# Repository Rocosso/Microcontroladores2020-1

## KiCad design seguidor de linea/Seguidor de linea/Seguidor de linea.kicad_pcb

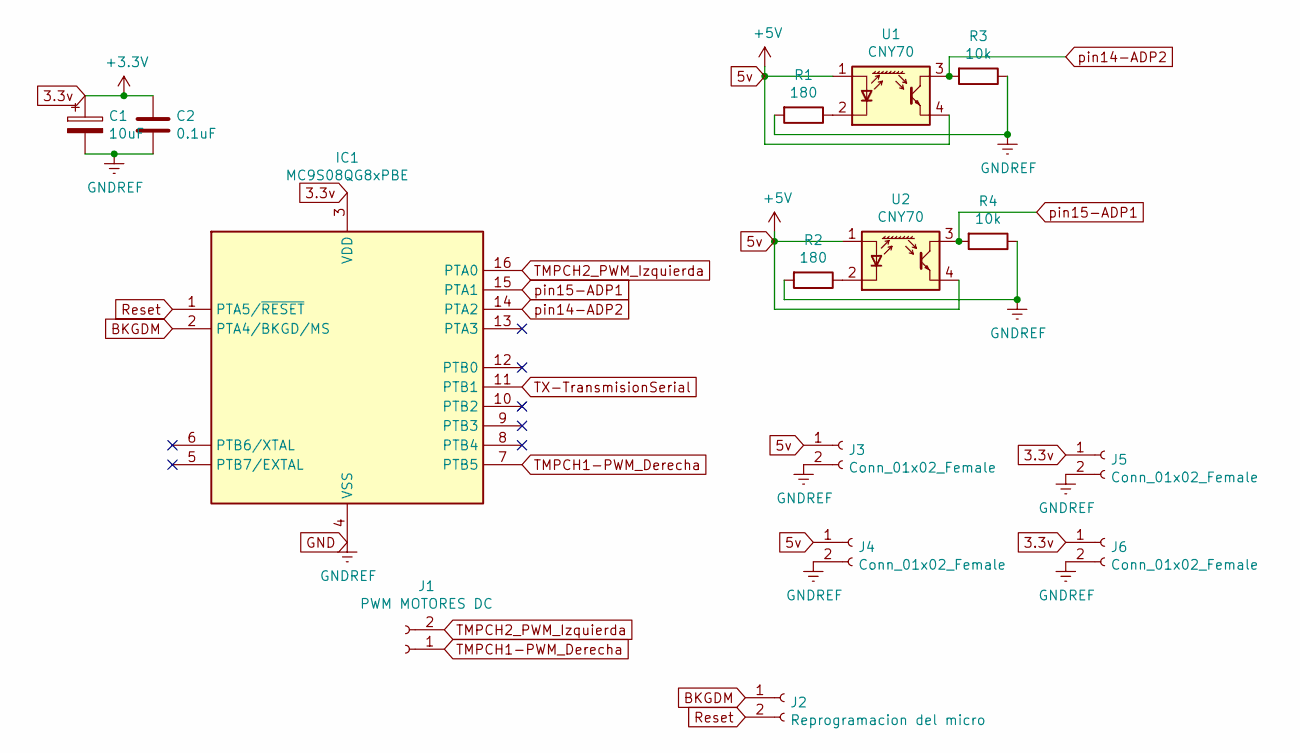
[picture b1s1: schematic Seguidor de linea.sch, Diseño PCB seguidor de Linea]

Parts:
C1: 10uF; CP_Radial_D4.0mm_P2.00mm
C2: 0.1uF; C_Disc_D4.7mm_W2.5mm_P5.00mm
IC1: MC9S08QG8xPBE; DIP-16_W7.62mm
J1: PWM MOTORES DC; PinSocket_1x02_P2.54mm_Vertical_SMD_Pin1Left
J2: Reprogramacion del micro; PinSocket_1x02_P2.54mm_Vertical_SMD_Pin1Left
J3, J4, J5, J6: Conn_01x02_Female; PinSocket_1x02_P2.54mm_Vertical_SMD_Pin1Right
R1, R2: 180; R_Axial_DIN0204_L3.6mm_D1.6mm_P1.90mm_Vertical
R3, R4: 10k; R_Axial_DIN0204_L3.6mm_D1.6mm_P1.90mm_Vertical
U1, U2: CNY70; Vishay_CNY70

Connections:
3.3v: C1.1, C2.1, IC1.3 (VDD), J5.1, J6.1
5v: J3.1, J4.1, U1.1 (A), U1.4 (E), U2.1 (A), U2.4 (E)
BKGDM: IC1.2 (PTA4/BKGD/MS), J2.1
GND: C1.2, C2.2, IC1.4 (VSS), J3.2, J4.2, J5.2, J6.2, R1.2, R2.2, R3.1, R4.1
unnamed: R1.1, U1.2 (K)
unnamed: R2.1, U2.2 (K)
Reset: IC1.1 (PTA5/~RESET), J2.2
TMPCH1-PWM_Derecha: IC1.7 (PTB5), J1.1
TMPCH2_PWM_Izquierda: IC1.16 (PTA0), J1.2
TX-TransmisionSerial: IC1.11 (PTB1)
pin14-ADP2: IC1.14 (PTA2), R3.2, U1.3 (C)
pin15-ADP1: IC1.15 (PTA1), R4.2, U2.3 (C)

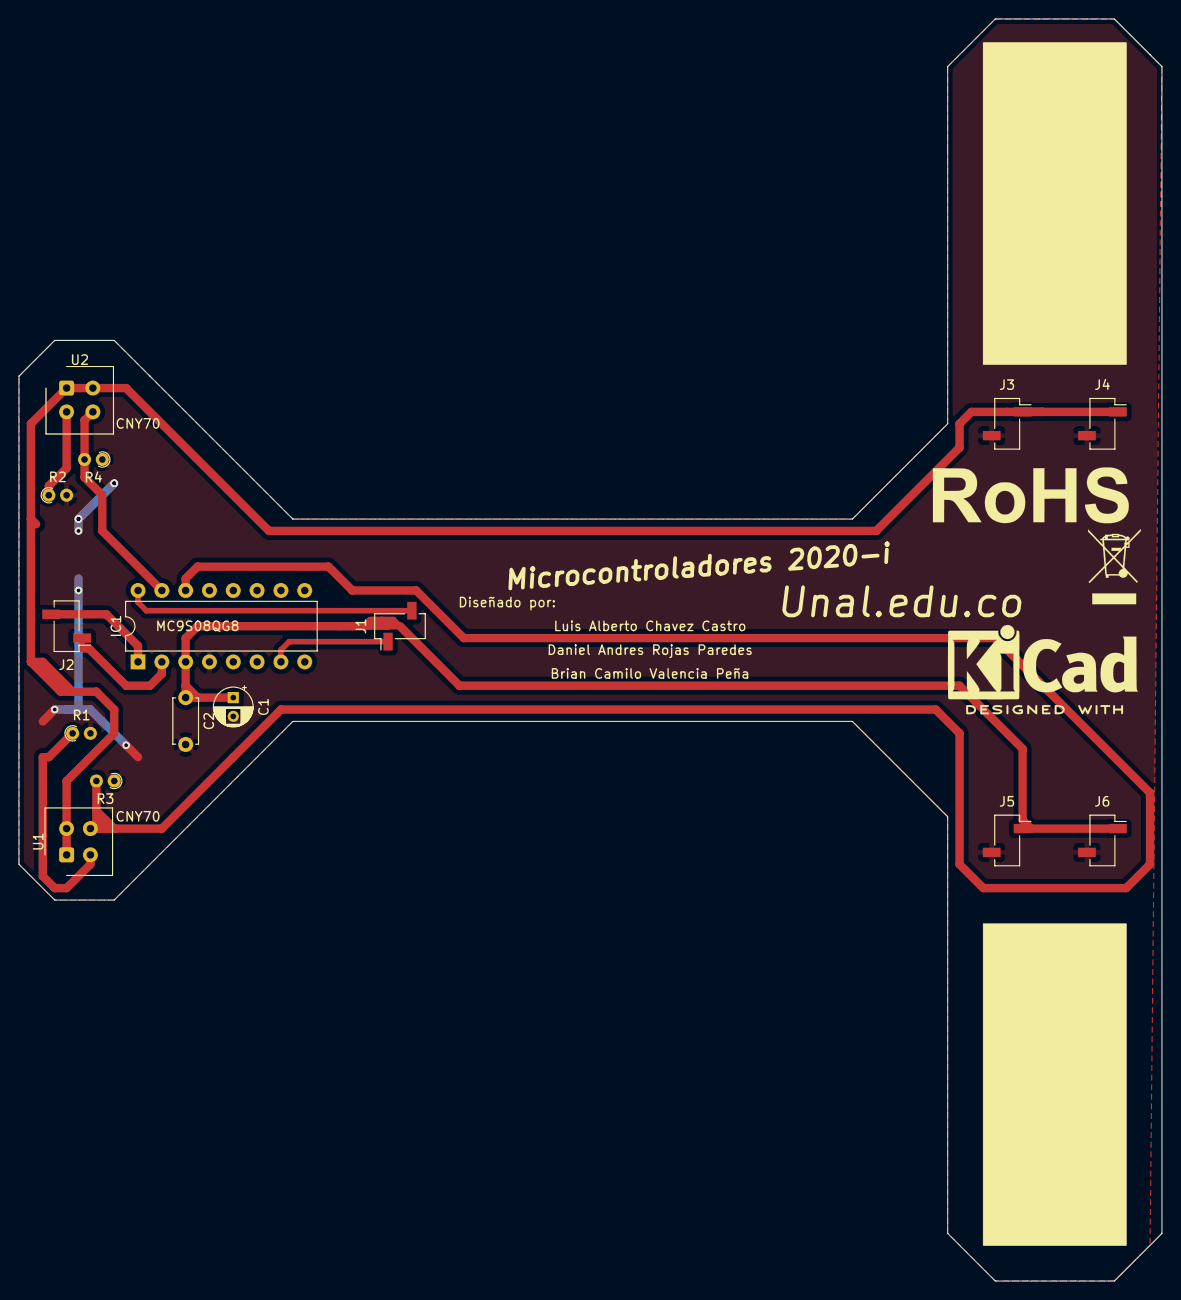
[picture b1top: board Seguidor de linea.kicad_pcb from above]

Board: 2 copper layers, 121.9 x 134.6 mm, 15 parts (0 on the bottom side), 11 nets.

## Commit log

2020-05-07 creacion del repositorio de microcontroladores
2020-05-07 creado el link al informe en overleaf
2020-05-07 actualizacion esquematico correccion tierra en LED-RGB e imagenes para el informe
2020-05-07 avance del PDF del informe del lab 1
2020-05-07 creacion carpeta lab2 y enlaces
2020-05-17 se actualizo en lab1 las fuentes de poder a 3v3, imagenes y esquematico
2020-05-17 agregados condensadores entre VCC y Vdd al esquematico
2020-05-17 se crea carpeta REFERENCE MANUAL CON DOS LIBROS, QG8 y HC08
2020-05-17 actualizacion de plantilla IEEE y correccion de errores en Overleaf
2020-05-17 creacion del proyecto lab1 en codewarrior 6.3
2020-05-18 se adjuntan las guias de trabajo de las 3 primeras practicas
2020-05-24 subi la carpeta que les envie al git, para no reenviarla, la ignoro en el gitignore
2020-05-31 LAB2
    Aca estan los arrchivos del codewarrior 6.3
2020-06-01 link reparado al documento LateX
2020-06-03 actualizacion del diseño de software en DIA en la carpeta lab3
2020-06-03 agregado .gitignore reparando la rama
2020-06-03 .gitignore
2020-06-04 prueba de correccion de un error
2020-06-04 corregido el error
2020-06-04 esquematico lab3
2020-06-04 link a plantilla online para el informe
2020-06-05 actualizacion archivo diagrama_lab_3
2020-06-09 guia 4 en carpetaa lab4
2020-06-09 carpeta seguidor de linea con imagenes protoideas
2020-06-09 hallados archivos de instrucciones para programacion del lab 3
2020-06-13 link laboratorio 4 informe
2020-06-16 carpeta con el lab4 para codewarrior 6.3
2020-06-23 re subida de la carpeta del lab4
2020-06-23 Create CODIGO OVERLEAFE
2020-06-28 lab 5 y lab 6
2020-06-30 RGB configurations
    organice los intervlor y pines para que se prendan los colores correctos
2020-07-02 mi version del lab5
2020-07-04 seguidor de linea
2020-07-04 seguidor de linea 2
2020-07-04 pdf y cad del seguidor de linea, con planos explosionados
